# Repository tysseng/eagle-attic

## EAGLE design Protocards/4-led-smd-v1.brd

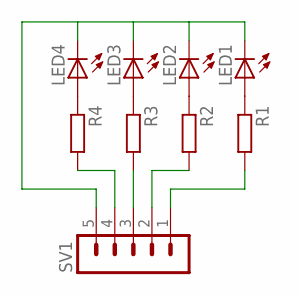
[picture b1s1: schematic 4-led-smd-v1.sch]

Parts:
LED1, LED2, LED3, LED4: LEDCHIP-LED0603; CHIP-LED0603
R1, R2, R3, R4: R-EU_R0603; R0603
SV1: MA05-1

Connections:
unnamed: LED4.A, R4.1
unnamed: LED1.A, R1.1
unnamed: LED2.A, R2.1
unnamed: LED3.A, R3.1
unnamed: LED1.C, LED2.C, LED3.C, LED4.C, SV1.5
unnamed: R3.2, SV1.3
unnamed: R2.2, SV1.2
unnamed: R1.2, SV1.1
unnamed: R4.2, SV1.4

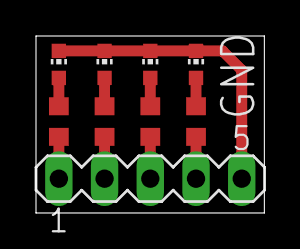
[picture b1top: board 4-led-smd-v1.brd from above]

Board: 2 copper layers, 12.7 x 9.8 mm, 9 parts (0 on the bottom side), 9 nets.

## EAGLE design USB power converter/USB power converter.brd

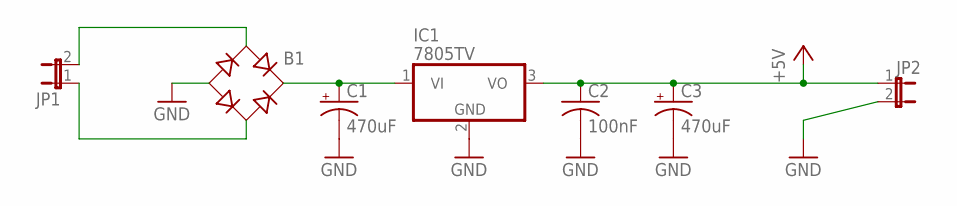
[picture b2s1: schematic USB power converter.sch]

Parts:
B1: RB1A
C1, C3: 470uF; E3,5-8
C2: 100nF; C025-024X044
IC1: 7805TV; TO220V
JP1, JP2: JP1E; JP1

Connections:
+5V: C2.1, C3.+, IC1.3 (VO), JP2.1
GND: B1.-, C1.-, C2.2, C3.-, IC1.2 (GND), JP2.2
unnamed: B1.AC1, JP1.2
unnamed: B1.AC2, JP1.1
unnamed: B1.+, C1.+, IC1.1 (VI)

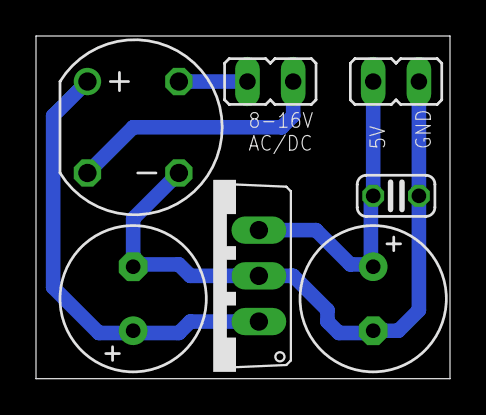
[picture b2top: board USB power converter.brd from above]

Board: 2 copper layers, 23.0 x 19.0 mm, 7 parts (0 on the bottom side), 5 nets.
